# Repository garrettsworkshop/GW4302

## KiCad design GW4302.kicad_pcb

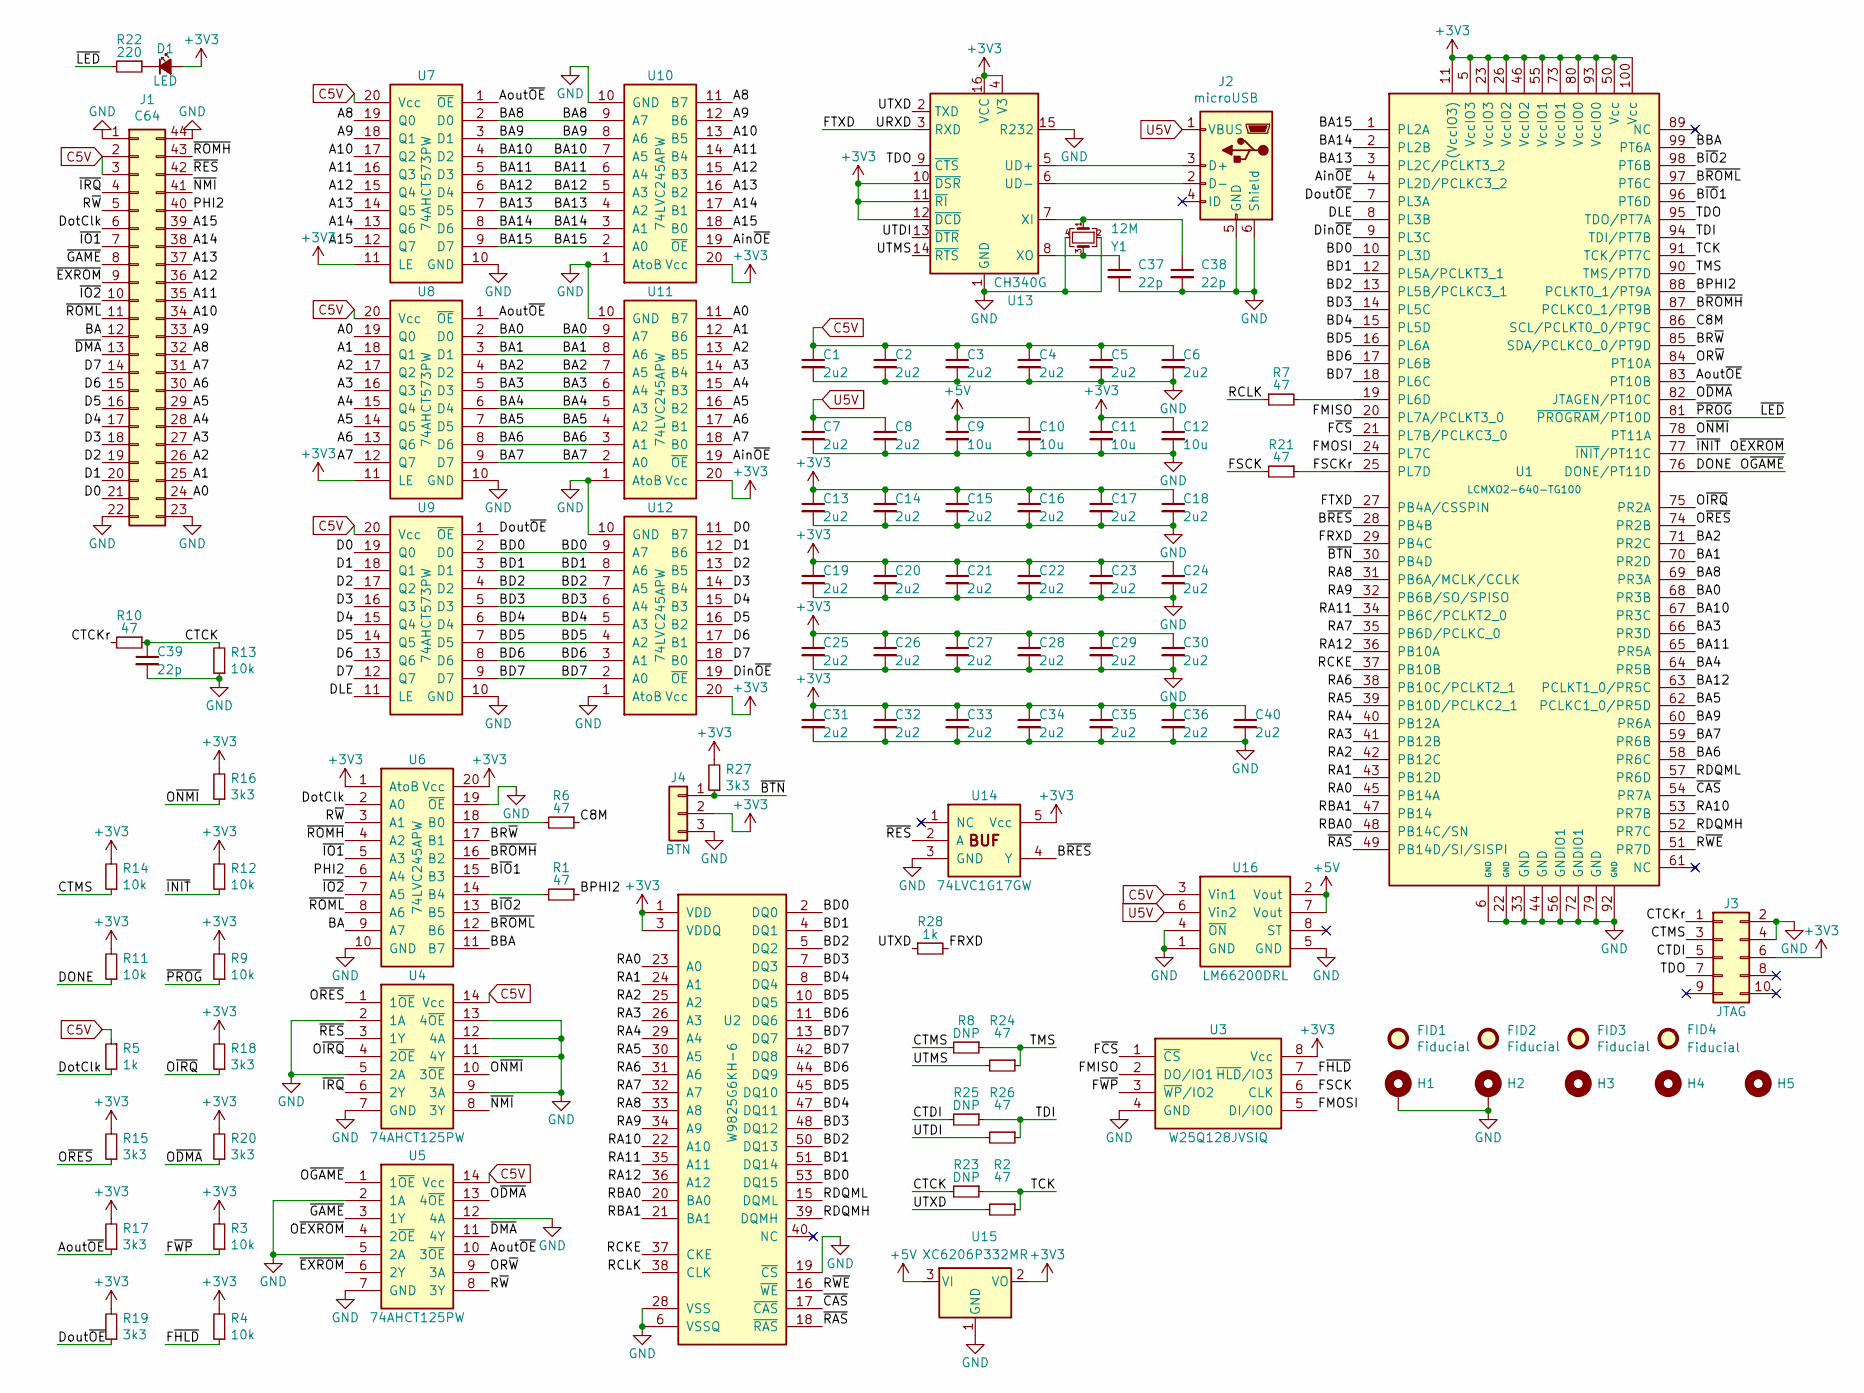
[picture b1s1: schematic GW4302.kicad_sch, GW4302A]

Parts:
C1, C2, C3, C4, C5, C6, C7, C8, C13, C14, C15, C16, C17, C18, C19, C20, C21, C22, C23, C24, C25, C26, C27, C28, C29, C30, C31, C32, C33, C34, C35, C36, C40: 2u2; C_0603; LCSC Part C23630
C9, C10, C11, C12: 10u; C_0805; LCSC Part C15850
C37, C38, C39: 22p; C_0603; LCSC Part C1653
D1: LED; LED_0805; LCSC Part C284932
FID1, FID2, FID3, FID4: Fiducial
H1, H2: PasteHole_1.1mm_PTH
H3, H4, H5: PasteHole_1.152mm_NPTH
J1: C64; AppleIIgsMemoryExpansion_Edge
J2: microUSB; USB_Micro-B_Amphenol_10118192-0001; LCSC Part C132564
J3: JTAG; Tag-Connect_TC2050-IDC-FP_2x05_P1.27mm_Vertical
J4: BTN; PinHeader_1x03_P2.00mm_Vertical
R1, R2, R6, R7, R10, R21, R24, R26: 47; R_0603; LCSC Part C23182
R3, R4, R9, R11, R12, R13, R14: 10k; R_0603; LCSC Part C25804
R5, R28: 1k; R_0603; LCSC Part C21190
R8, R23, R25: DNP; R_0603
R15, R16, R17, R18, R19, R20, R27: 3k3; R_0603; LCSC Part C22978
R22: 220; R_0805; LCSC Part C17557
U1: LCMXO2-640-TG100; TQFP-100_14x14mm_P0.5mm; LCSC Part C1521611
U2: W9825G6KH-6; TSOP-II-54_22.2x10.16mm_P0.8mm; LCSC Part C62246
U3: W25Q128JVSIQ; SOIC-8_5.3mm; LCSC Part C97521
U4, U5: 74AHCT125PW; TSSOP-14_4.4x5mm_P0.65mm; LCSC Part C36365
U6, U10, U11, U12: 74LVC245APW; TSSOP-20_4.4x6.5mm_P0.65mm; LCSC Part C7848
U7, U8, U9: 74AHCT573PW; TSSOP-20_4.4x6.5mm_P0.65mm; LCSC Part C141311
U13: CH340G; SOIC-16_3.9mm; LCSC Part C14267
U14: 74LVC1G17GW; SOT-353; LCSC Part C426705
U15: XC6206P332MR; SOT-23; LCSC Part C5446
U16: LM66200DRL; SOT-583; LCSC Part C3235556
Y1: 12M; Crystal_SMD_3225-4Pin_3.2x2.5mm; LCSC Part C9002

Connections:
+3V3: C11.1, C12.1, C13.1, C14.1, C15.1, C16.1, C17.1, C18.1, C19.1, C20.1, C21.1, C22.1, C23.1, C24.1, C25.1, C26.1, C27.1, C28.1, C29.1, C30.1, C31.1, C32.1, C33.1, C34.1, C35.1, C36.1, C40.1, D1.2 (A), J3.6, J4.2, R3.2, R4.2, R9.2, R11.2, R12.2, R14.2, R15.2, R16.2, R17.2, R18.2, R19.2, R20.2, R27.2, U1.5 (VccIO3), U1.11 ((VccIO3)), U1.23 (VccIO3), U1.26 (VccIO2), U1.46 (VccIO2), U1.50 (Vcc), U1.55 (VccIO1), U1.73 (VccIO1), U1.80 (VccIO0), U1.93 (VccIO0), U1.100 (Vcc), U2.1 (VDD), U2.3 (VDDQ), U2.9 (VDDQ), U2.14 (VDD), U2.27 (VDD), U2.43 (VDDQ), U2.49 (VDDQ), U3.8 (Vcc), U6.1 (AtoB), U6.20 (Vcc), U7.11 (LE), U8.11 (LE), U10.20 (Vcc), U11.20 (Vcc), U12.20 (Vcc), U13.4 (V3), U13.10 (~DSR), U13.11 (~RI), U13.12 (~DCD), U13.16 (VCC), U14.5 (Vcc), U15.2 (VO)
+5V: C9.1, C10.1, U15.3 (VI), U16.2 (Vout), U16.7 (Vout)
/A0: J1.24, U8.19 (Q0), U11.11 (B7)
/A1: J1.25, U8.18 (Q1), U11.12 (B6)
/A2: J1.26, U8.17 (Q2), U11.13 (B5)
/A3: J1.27, U8.16 (Q3), U11.14 (B4)
/A4: J1.28, U8.15 (Q4), U11.15 (B3)
/A5: J1.29, U8.14 (Q5), U11.16 (B2)
/A6: J1.30, U8.13 (Q6), U11.17 (B1)
/A7: J1.31, U8.12 (Q7), U11.18 (B0)
/A8: J1.32, U7.19 (Q0), U10.11 (B7)
/A9: J1.33, U7.18 (Q1), U10.12 (B6)
/A10: J1.34, U7.17 (Q2), U10.13 (B5)
/A11: J1.35, U7.16 (Q3), U10.14 (B4)
/A12: J1.36, U7.15 (Q4), U10.15 (B3)
/A13: J1.37, U7.14 (Q5), U10.16 (B2)
/A14: J1.38, U7.13 (Q6), U10.17 (B1)
/A15: J1.39, U7.12 (Q7), U10.18 (B0)
/Ain~OE: U1.4 (PL2D/PCLKC3_2), U10.19 (~OE), U11.19 (~OE)
/Aout~OE: R17.1, U1.83 (PT10B), U5.10 (3~OE), U7.1 (~OE), U8.1 (~OE)
/BA: J1.12, U6.9 (A7)
/BA0: U1.68 (PR3B), U8.2 (D0), U11.9 (A7)
/BA1: U1.70 (PR2D), U8.3 (D1), U11.8 (A6)
/BA2: U1.71 (PR2C), U8.4 (D2), U11.7 (A5)
/BA3: U1.66 (PR3D), U8.5 (D3), U11.6 (A4)
/BA4: U1.64 (PR5B), U8.6 (D4), U11.5 (A3)
/BA5: U1.62 (PCLKC1_0/PR5D), U8.7 (D5), U11.4 (A2)
/BA6: U1.58 (PR6C), U8.8 (D6), U11.3 (A1)
/BA7: U1.59 (PR6B), U8.9 (D7), U11.2 (A0)
/BA8: U1.69 (PR3A), U7.2 (D0), U10.9 (A7)
/BA9: U1.60 (PR6A), U7.3 (D1), U10.8 (A6)
/BA10: U1.67 (PR3C), U7.4 (D2), U10.7 (A5)
/BA11: U1.65 (PR5A), U7.5 (D3), U10.6 (A4)
/BA12: U1.63 (PCLKT1_0/PR5C), U7.6 (D4), U10.5 (A3)
/BA13: U1.3 (PL2C/PCLKT3_2), U7.7 (D5), U10.4 (A2)
/BA14: U1.2 (PL2B), U7.8 (D6), U10.3 (A1)
/BA15: U1.1 (PL2A), U7.9 (D7), U10.2 (A0)
/BBA: U1.99 (PT6A), U6.11 (B7)
/BD0: U1.10 (PL3D), U2.2 (DQ0), U2.53 (DQ15), U9.2 (D0), U12.9 (A7)
/BD1: U1.12 (PL5A/PCLKT3_1), U2.4 (DQ1), U2.51 (DQ14), U9.3 (D1), U12.8 (A6)
/BD2: U1.13 (PL5B/PCLKC3_1), U2.5 (DQ2), U2.50 (DQ13), U9.4 (D2), U12.7 (A5)
/BD3: U1.14 (PL5C), U2.7 (DQ3), U2.48 (DQ12), U9.5 (D3), U12.6 (A4)
/BD4: U1.15 (PL5D), U2.8 (DQ4), U2.47 (DQ11), U9.6 (D4), U12.5 (A3)
/BD5: U1.16 (PL6A), U2.10 (DQ5), U2.45 (DQ10), U9.7 (D5), U12.4 (A2)
/BD6: U1.17 (PL6B), U2.11 (DQ6), U2.44 (DQ9), U9.8 (D6), U12.3 (A1)
/BD7: U1.18 (PL6C), U2.13 (DQ7), U2.42 (DQ8), U9.9 (D7), U12.2 (A0)
/BPHI2: R1.1, U1.88 (PCLKT0_1/PT9A)
/BR~W: U1.85 (SDA/PCLKC0_0/PT9D), U6.17 (B1)
/B~IO1: U1.96 (PT6D), U6.15 (B3)
/B~IO2: U1.98 (PT6B), U6.13 (B5)
/B~RES: U1.28 (PB4B), U14.4 (Y)
/B~ROMH: U1.87 (PCLKC0_1/PT9B), U6.16 (B2)
/B~ROML: U1.97 (PT6C), U6.12 (B6)
/C8M: R6.1, U1.86 (SCL/PCLKT0_0/PT9C)
/CTCK: C39.1, R10.1, R13.2, R23.2
/CTCKr: J3.1, R10.2
/CTDI: J3.5, R25.2
/CTMS: J3.3, R8.2, R14.1
/D0: J1.21, U9.19 (Q0), U12.11 (B7)
/D1: J1.20, U9.18 (Q1), U12.12 (B6)
/D2: J1.19, U9.17 (Q2), U12.13 (B5)
/D3: J1.18, U9.16 (Q3), U12.14 (B4)
/D4: J1.17, U9.15 (Q4), U12.15 (B3)
/D5: J1.16, U9.14 (Q5), U12.16 (B2)
/D6: J1.15, U9.13 (Q6), U12.17 (B1)
/D7: J1.14, U9.12 (Q7), U12.18 (B0)
/DLE: U1.8 (PL3B), U9.11 (LE)
/DONE: R11.1, U1.76 (DONE/PT11D), U5.1 (1~OE)
/Din~OE: U1.9 (PL3C), U12.19 (~OE)
/DotClk: J1.6, R5.2, U6.2 (A0)
/Dout~OE: R19.1, U1.7 (PL3A), U9.1 (~OE)
/FMISO: U1.20 (PL7A/PCLKT3_0), U3.2 (DO/IO1)
/FMOSI: U1.24 (PL7C), U3.5 (DI/IO0)
/FRXD: R28.2, U1.29 (PB4C)
/FSCK: R21.2, U3.6 (CLK)
/FSCKr: R21.1, U1.25 (PL7D)
/FTXD: U1.27 (PB4A/CSSPIN), U13.3 (RXD)
/F~CS: U1.21 (PL7B/PCLKC3_0), U3.1 (~CS)
/F~HLD: R4.1, U3.7 (~HLD/IO3)
/F~WP: R3.1, U3.3 (~WP/IO2)
/OR~W: U1.84 (PT10A), U5.9 (3A)
/O~DMA: R20.1, U1.82 (JTAGEN/PT10C), U5.13 (4~OE)
/O~EXROM: R12.1, U1.77 (~INIT/PT11C), U5.4 (2~OE)
/O~IRQ: R18.1, U1.75 (PR2A), U4.4 (2~OE)
/O~NMI: R16.1, U1.78 (PT11A), U4.10 (3~OE)
/O~RES: R15.1, U1.74 (PR2B), U4.1 (1~OE)
/PHI2: J1.40, U6.6 (A4)
/RA0: U1.45 (PB14A), U2.23 (A0)
/RA1: U1.43 (PB12D), U2.24 (A1)
/RA2: U1.42 (PB12C), U2.25 (A2)
/RA3: U1.41 (PB12B), U2.26 (A3)
/RA4: U1.40 (PB12A), U2.29 (A4)
/RA5: U1.39 (PB10D/PCLKC2_1), U2.30 (A5)
/RA6: U1.38 (PB10C/PCLKT2_1), U2.31 (A6)
/RA7: U1.35 (PB6D/PCLKC_0), U2.32 (A7)
/RA8: U1.31 (PB6A/MCLK/CCLK), U2.33 (A8)
/RA9: U1.32 (PB6B/SO/SPISO), U2.34 (A9)
/RA10: U1.53 (PR7B), U2.22 (A10)
/RA11: U1.34 (PB6C/PCLKT2_0), U2.35 (A11)
/RA12: U1.36 (PB10A), U2.36 (A12)
/RBA0: U1.48 (PB14C/SN), U2.20 (BA0)
/RBA1: U1.47 (PB14), U2.21 (BA1)
/RCKE: U1.37 (PB10B), U2.37 (CKE)
/RCLK: R7.1, U2.38 (CLK)
/RDQMH: U1.52 (PR7C), U2.39 (DQMH)
/RDQML: U1.57 (PR6D), U2.15 (DQML)
/R~WE: U1.51 (PR7D), U2.16 (~WE)
/R~W: J1.5, U5.8 (3Y), U6.3 (A1)
/TCK: R2.1, R23.1, U1.91 (TCK/PT7C)
/TDI: R25.1, R26.1, U1.94 (TDI/PT7B)
/TDO: J3.7, U1.95 (TDO/PT7A), U13.9 (~CTS)
/TMS: R8.1, R24.1, U1.90 (TMS/PT7D)
/UTDI: R26.2, U13.13 (~DTR)
/UTMS: R24.2, U13.14 (~RTS)
/UTXD: R2.2, R28.1, U13.2 (TXD)
/~BTN: J4.1, R27.1, U1.30 (PB4D)
/~CAS: U1.54 (PR7A), U2.17 (~CAS)
/~DMA: J1.13, U5.11 (4Y)
/~EXROM: J1.9, U5.6 (2Y)
/~GAME: J1.8, U5.3 (1Y)
/~IO1: J1.7, U6.5 (A3)
/~IO2: J1.10, U6.7 (A5)
/~IRQ: J1.4, U4.6 (2Y)
/~LED: R9.1, R22.2, U1.81 (~PROGRAM/PT10D)
/~NMI: J1.41, U4.8 (3Y)
/~RAS: U1.49 (PB14D/SI/SISPI), U2.18 (~RAS)
/~RES: J1.42, U4.3 (1Y), U14.2 (A)
/~ROMH: J1.43, U6.4 (A2)
/~ROML: J1.11, U6.8 (A6)
C5V: C1.1, C2.1, C3.1, C4.1, C5.1, C6.1, J1.2, J1.3, R5.1, U4.14 (Vcc), U5.14 (Vcc), U7.20 (Vcc), U8.20 (Vcc), U9.20 (Vcc), U16.3 (Vin1)
GND: C1.2, C2.2, C3.2, C4.2, C5.2, C6.2, C7.2, C8.2, C9.2, C10.2, C11.2, C12.2, C13.2, C14.2, C15.2, C16.2, C17.2, C18.2, C19.2, C20.2, C21.2, C22.2, C23.2, C24.2, C25.2, C26.2, C27.2, C28.2, C29.2, C30.2, C31.2, C32.2, C33.2, C34.2, C35.2, C36.2, C37.2, C38.2, C39.2, C40.2, H1.1, H2.1, J1.1, J1.22, J1.23, J1.44, J2.5 (GND), J2.6 (Shield), J3.2, J3.4, J4.3, R13.1, U1.6 (GND), U1.22 (GND), U1.33 (GND), U1.44 (GND), U1.56 (GNDIO1), U1.72 (GNDIO1), U1.79 (GND), U1.92 (GND), U2.6 (VSSQ), U2.12 (VSSQ), U2.19 (~CS), U2.28 (VSS), U2.41 (VSS), U2.46 (VSSQ), U2.52 (VSSQ), U2.54 (VSS), U3.4 (GND), U4.2 (1A), U4.5 (2A), U4.7 (GND), U4.9 (3A), U4.11 (4Y), U4.12 (4A), U4.13 (4~OE), U5.2 (1A), U5.5 (2A), U5.7 (GND), U5.12 (4A), U6.10 (GND), U6.19 (~OE), U7.10 (GND), U8.10 (GND), U9.10 (GND), U10.1 (AtoB), U10.10 (GND), U11.1 (AtoB), U11.10 (GND), U12.1 (AtoB), U12.10 (GND), U13.1 (GND), U13.15 (R232), U14.3 (GND), U15.1 (GND), U16.1 (GND), U16.4 (~ON), U16.5 (GND), Y1.2, Y1.4
unnamed: D1.1 (K), R22.1
unnamed: J2.3 (D+), U13.5 (UD+)
unnamed: J2.2 (D-), U13.6 (UD-)
unnamed: R7.2, U1.19 (PL6D)
unnamed: R6.2, U6.18 (B0)
unnamed: R1.2, U6.14 (B4)
unnamed: C38.1, U13.7 (XI), Y1.1
unnamed: C37.1, U13.8 (XO), Y1.3
U5V: C7.1, C8.1, J2.1 (VBUS), U16.6 (Vin2)

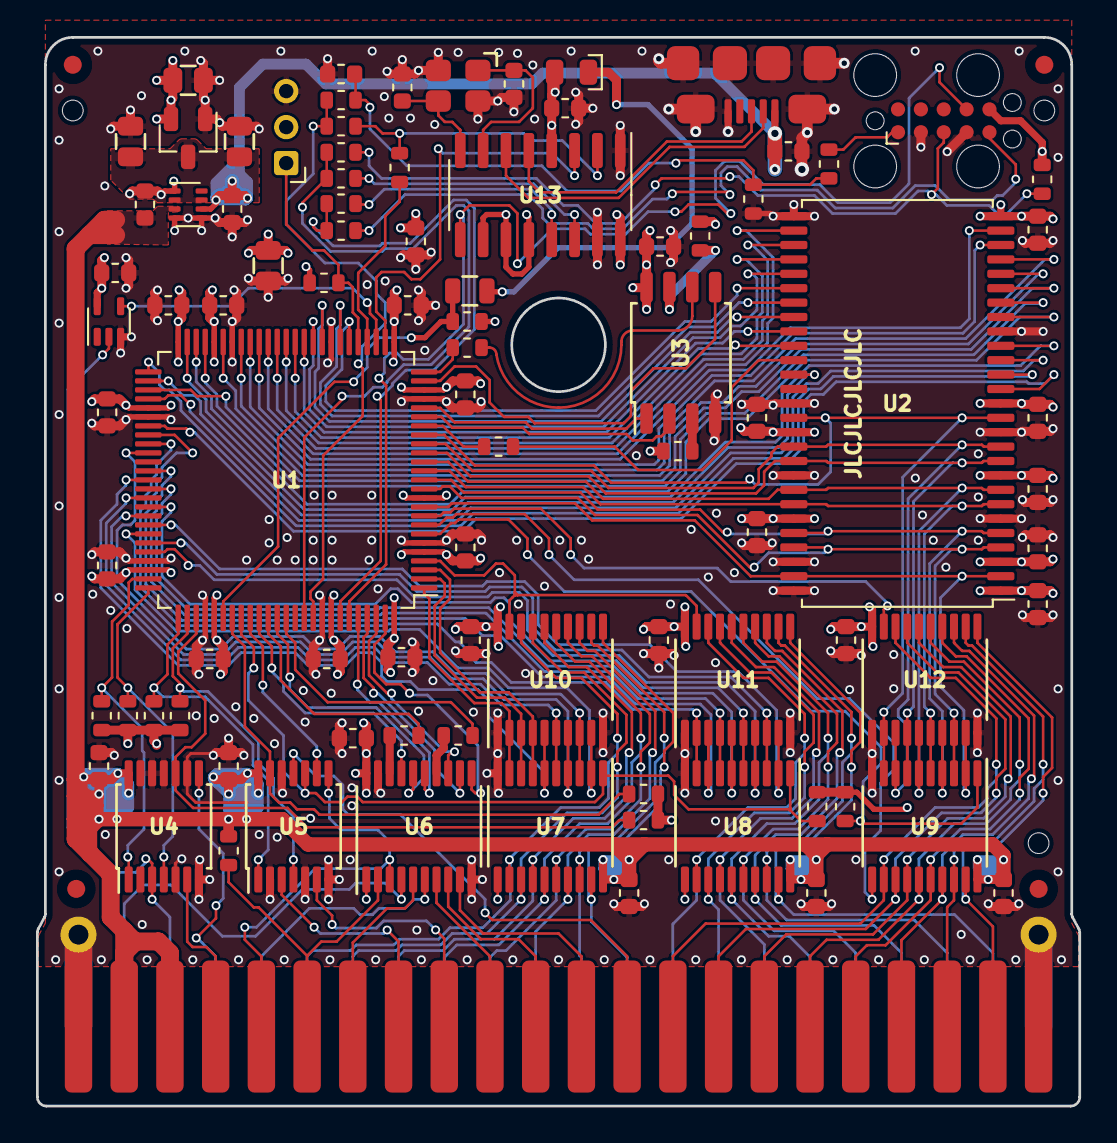
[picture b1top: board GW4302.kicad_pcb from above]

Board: 4 copper layers, 57.9 x 59.4 mm, 99 parts (1 on the bottom side), 140 nets.

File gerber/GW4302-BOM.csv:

"Reference","Quantity","Value","Footprint","LCSC Part","DNP"
"C1, C2, C3, C4, C5, C6, C7, C8, C13, C14, C15, C16, C17, C18, C19, C20, C21, C22, C23, C24, C25, C26, C27, C28, C29, C30, C31, C32, C33, C34, C35, C36, C40","33","2u2","stdpads:C_0603","C23630",""
"C9, C10, C11, C12","4","10u","stdpads:C_0805","C15850",""
"C37, C38, C39","3","22p","stdpads:C_0603","C1653",""
"D1","1","LED","stdpads:LED_0805","C284932",""
"FID1, FID2, FID3, FID4","4","Fiducial","stdpads:Fiducial","",""
"H1, H2","2","~","stdpads:PasteHole_1.1mm_PTH","",""
"H3, H4, H5","3","~","stdpads:PasteHole_1.152mm_NPTH","",""
"J1","1","C64","stdpads:AppleIIgsMemoryExpansion_Edge","",""
"J2","1","microUSB","stdpads:USB_Micro-B_Amphenol_10118192-0001","C132564",""
"J3","1","JTAG","stdpads:Tag-Connect_TC2050-IDC-FP_2x05_P1.27mm_Vertical","",""
"J4","1","BTN","stdpads:PinHeader_1x03_P2.00mm_Vertical","",""
"R1, R2, R6, R7, R10, R21, R24, R26","8","47","stdpads:R_0603","C23182",""
"R3, R4, R9, R11, R12, R13, R14","7","10k","stdpads:R_0603","C25804",""
"R5, R28","2","1k","stdpads:R_0603","C21190",""
"R8, R23, R25","3","DNP","stdpads:R_0603","",""
"R15, R16, R17, R18, R19, R20, R27","7","3k3","stdpads:R_0603","C22978",""
"R22","1","220","stdpads:R_0805","C17557",""
"U1","1","LCMXO2-640-TG100","stdpads:TQFP-100_14x14mm_P0.5mm","C1521611",""
"U2","1","W9825G6KH-6","stdpads:TSOP-II-54_22.2x10.16mm_P0.8mm","C62246",""
"U3","1","W25Q128JVSIQ","stdpads:SOIC-8_5.3mm","C97521",""
"U4, U5","2","74AHCT125PW","stdpads:TSSOP-14_4.4x5mm_P0.65mm","C36365",""
"U6, U10, U11, U12","4","74LVC245APW","stdpads:TSSOP-20_4.4x6.5mm_P0.65mm","C7848",""
"U7, U8, U9","3","74AHCT573PW","stdpads:TSSOP-20_4.4x6.5mm_P0.65mm","C141311",""
"U13","1","CH340G","stdpads:SOIC-16_3.9mm","C14267",""
"U14","1","74LVC1G17GW","stdpads:SOT-353","C426705",""
"U15","1","XC6206P332MR","stdpads:SOT-23","C5446",""
"U16","1","LM66200DRL","stdpads:SOT-583","C3235556",""
"Y1","1","12M","stdpads:Crystal_SMD_3225-4Pin_3.2x2.5mm","C9002",""

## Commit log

2022-01-02 Changed documentation folder to docs
2022-01-15 As submitted to JLC
2022-01-18 Draft of RAM and registers verilog
2022-01-18 Fix length register
2022-01-18 Just syntactic changes
2022-01-18 Add autoload functionality
2022-01-18 Starting on DMA sequencer
2022-01-18 More DMA sequencer control
2022-01-18 Fix timing diagram 6B NextREUA signal
2022-01-18 Update GW4302.sch
    Change from 'LVC to 'AHC for non-edge triggered signal buffering
2022-01-18 Syntax changes
2022-01-18 Simplified DMA sequencer logic
2022-01-19 Rearrange parameters in DMASeq.v
2022-01-19 Name changes in RAM.v
2022-01-19 Add IRQ to Reg.v
2022-01-19 Fix indices in Reg.v
2022-01-19 Compiles. 345 LEs
2022-01-19 Fix asynchronous stuff in timing diagrams
2022-01-19 Fix JTAG connections on board
2022-02-01 Migrate to KiCAD 6
2022-02-06 Move documentation
2022-02-06 CPLD stuff
2022-02-07 Create LICENSE
2022-04-22 Clearable size bit
2022-04-23 dumb
2022-04-23 Fix DDIR equation
2022-04-23 Disable DMA engine
2022-04-23 Actually fixed DOE
2022-04-23 Works a lot better now
2022-04-24 Better
2022-04-25 RAM bugfixes
    Replace PLLLock with PORDone. PORDone activation is not dependent on S[2:0].
    Don't increment S[2:0] until PORDone.
    Change RAM command issue table accordingly.
2022-04-25 Better sequencing
2022-04-26 Update DMASeq.v
    Fix verify increment after not equal
2022-04-26 Fix non-verify stop bug
2022-04-26 Set end of block during transfer of length 1
2022-04-26 Many more improvements plus lots of comments
2022-04-27 nothing really lol
2022-04-27 Add geoRAM implementation
2022-04-28 Better georam
2022-04-28 Clean up geoRAM implemenation
2022-04-28 georam stuff idk
2022-04-28 Cut down thought for macrocell-based PLDs
2022-04-28 Removed macrocell PLD stuff
2022-04-28 Fixed
2022-04-29 Put back buffer /OE control
2022-09-17 Add SVF
2022-09-18 Update Reg.v
    idk formatting
2022-09-18 Add pull-up resistors on AOE, DOE, IRQOE, RESOE
2022-09-19 Switch to 3225 crystal for USB
2022-09-19 Update sym-lib-table
2023-02-13 Fix board ID
2023-03-22 Revert "??"
    This reverts commit 2eec9a9f33069042b41c52556303140318240893.
2024-02-16 Create Makefile
2024-02-16 Done?
2024-02-16 Update Makefile
    change "GW4302B" in filenames to "GW4302A"
2024-02-16 As sent to JLC
2024-03-18 Update Makefile
2024-03-18 Rebuild to generate BOM but no board changes
2025-01-10 New version
